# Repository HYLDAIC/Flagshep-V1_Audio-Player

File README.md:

# Flagshep V1 Audio Player

*During Playback*

## Overview
The **Flagshep** is a semi-portable open-source Audio Player designed to provide a reliable, high-quality offline listening experience. It's purpose is to be an alternative to advertisement-ridden subscription based streaming services. The pilot project includes the PCB design files, enclosure CAD models and firmware source code required to build upon, modify or simply take inspiration of the device.

# Features & Specifications 
## Features
- High Quality Audio Diffusion 
- USB-C Charging and Flashing 
## Specifications 
- **Processor :** ESP32 S3 (2 Core 240MHz, 2.4 GHz Wi-Fi 150 Mbps, Bluetooth 5 (LE) )
- **Audio Quality :** PCM5102A ; 16-32bit at 8kHz to 384kHz
- **Flash :** 8MB quad SPI Flash
- **RAM :** 8MB quad SPI SRAM
- **Display :** 0.96in 128x64px OLED TFT display
- **Input :** 6 Button Matrix
- **Storage :** MicroSD card slot
- **Battery :** 5000mAh LiPo with integrated charging and battery management
- **Connectors :** USB Type-C and TRS 3.5mm Audio Jack
- **Dimensions :** 98.7 x 76.8 x 34.7 mm (length-width-height)

# Design 

## Hardware & Included Sensors
- **Microcontroller :** ESP32 S3 Wroom 1
- **DAC Chip :** PCM5102A
- **Battery charging & Protection :** TP4056 & DW01A + FS8205A
- **Voltage Regulator (LDO) :** AP2112K-3.3
- **Battery Percentage Chip :**  MAX17048G+T10
- **Battery Connector :** JST XH-B2B-A

*Logic Depiction of the Hardware*

## Firmware 
- A simple loop that handles button presses, screen refreshes, audio streaming and battery capacity/optimizations; fairly simple
- More coming soon to a town near you!

# Enclosure & Build Instructions (Doesn't include pictures)
- M4 screwdriver
- 3D printed parts (Main, Top of your choosing, and Bottom cover)
- The PCB
- A flat Lithium Polymer battery (LiPo) with the connector JST-XH 2 pin
- 12 6-8mm screws M4 screws
- 12 6x6mm (M4) threaded heated inserts
- Formatted SD Card (FAT32,  exFAT ...) with the audio of your choice (mp3, WAV, FLAC, AAC, m4a)
- A Computer (Linux and or Windows 10-11) with VS Code and Platformio installed
- USB-C Data cable
- Soldering iron

  1. The Main 3D printed part should have prominent holes, 8 on the front side and 4 in the back
  2. Prepare heated element to 250 degrees Celsius (+/- 30)
  3. Place and slowly push in the threaded heated insert with the soldering iron into the hole until the mounting surface is flat (repeat 12 times)
  4. If the battery connector of the PCB isn't on the bottom face (face with no components), solder it on the bottom making sure to keep the same polarities
  5. Insert the SD card in the SD card slot
  6. Take the PCB and insert it inside the side with 8 screws, it should fit with the bottom four; screw it on (it should match with the outside holes on the side of the Main piece)
  7. Insert and screw in the Top cover with 4 screws
  8. Insert a LiPo battery in the bottom compartment and plug it in
  9. Screw in the bottom cover making sure not to break the cable of your battery
  10. Take a USB-C data cable and plug it into the board and the computer
  11. Compile the code given in the Github repo (check tutorials online if you are not sure about how to do this)
  12. Flash the code

# Successes & Future Improvements (Hardware focused)
## Successes
- The audio is smooth and doesn't have noticeable glitching or noise within playback
- A battery life of about 32-40 hours on a 5000mAh battery (~35h of playback in an room varying from 23 to 35 degrees Celsius)
- A smooth user experience; fairly intuitive button mapping, responsive menus and UI (tested by passing my friends the player and receiving feedback)
- An easily accessible and removable battery/screen (4 Screws each)
- Fairly resistant; could be dropped several times with no issues to the PCB (1m drop height)
- The PCB worked first try :)

## Future Improvements
The design has notable failure points that can't be addressed in version 1.1 and would need a more substantial redesign, here are some :
- The circuit drains significant amounts of battery on sleeping parts when the microcontroller is sleeping; physical software activated kill switch needed
- Due to bad design around the battery; the enclosure is huge (height)
- The ESP32 S3 is realistically overkill for the scope of this project AND wireless isn't the focus and could've been avoided
- Components are way too close together making assembly difficult 
- The lack of a knobs proves more difficult than expected
- The screen is really small (this was intended but a more substantial screen could've been afforded under this battery capacity)
- Visible and protruding screws
- Somewhat Heavy (battery)
- The battery percentage chip has interference issues with nearby components and should be placed closer to the battery's connector
- Adding test pads for important signals

Issues that weren't but can be easily addressed in version 1.2 :
- Outside ports are hard to access (too far from outside ridge)
- Thermal relief for ground pads NEED to be added

Personal issues with the design : 
- Many parts of the circuit could have been separated on different boards to permit easy fixing and maintenance (e.g. board 1; power, board 2; logic, etc)

## Plans for the project
Apart from version 1.2, I plan to remake the audio player in a couple of years after I have learned more about circuit design and embedded development.
For now, all the following improvements made to this project will made in the form of sporadic software improvements as I catch problems or wants with the device in my own usage.

# License
The license only applies to the PCB part of the design, not the code nor the 3D STEP files which are unlicensed

# Acknowledgements
## Help & Design inspirations 
- My non-technical friends for support & UX feedback
- r/PrintedCircuits for help with circuit design (https://www.reddit.com/r/PrintedCircuitBoard/)
- PocketMage by Ashtf at Talisman Designs (specs & features section and general design inspiration) (https://www.crowdsupply.com/talisman-design/pocketmage)
## Firmware
- Adafruit (GFX & SSD1306)
- ESP32-audioI2S by Schreibfaul1 (https://github.com/schreibfaul1/ESP32-audioI2S)

## Special Mention
The large reason of why I decided to commit to making this audio player was for my love of music that I'm sure others can relate to.
That said, during the development of the board, one of my favorite band disbanded.
As an homage to them and what their music meant to me, I chose to immortalize them on the surface of my PCB with their most popular instrumental. 

Again, this is a small tribute, but it may just last forever ;)

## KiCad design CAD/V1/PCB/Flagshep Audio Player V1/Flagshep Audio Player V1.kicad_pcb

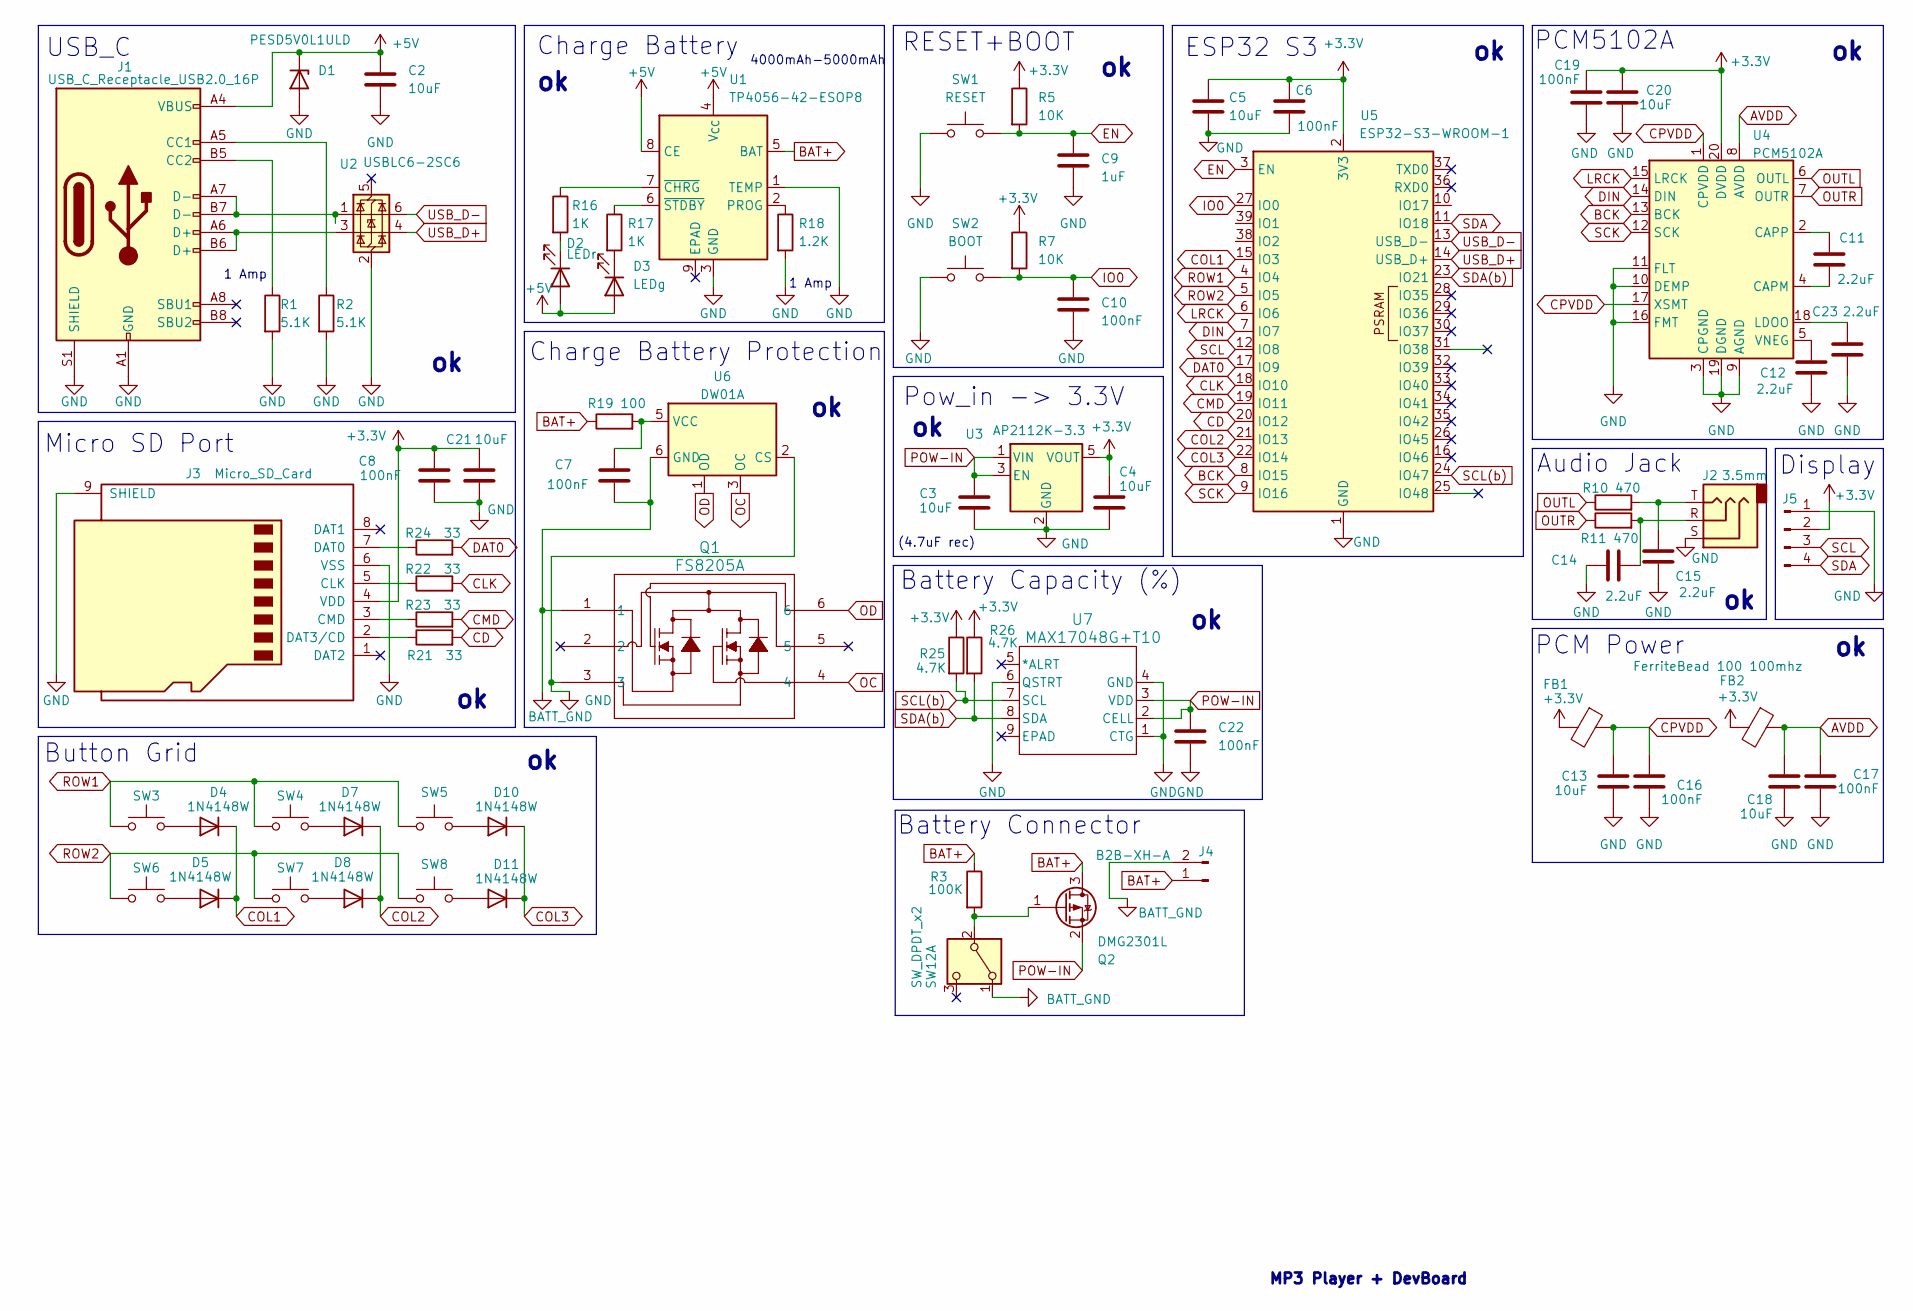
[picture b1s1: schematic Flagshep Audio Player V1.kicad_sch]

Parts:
C2, C13, C18, C20, C21: 10uF; C_0805_2012Metric_Pad1.18x1.45mm_HandSolder
C3, C4, C5: 10uF; R_0805_2012Metric_Pad1.20x1.40mm_HandSolder
C6: 100nF; R_0805_2012Metric_Pad1.20x1.40mm_HandSolder
C7, C8, C10, C16, C17, C19, C22: 100nF; C_0805_2012Metric_Pad1.18x1.45mm_HandSolder
C9: 1uF; R_0805_2012Metric_Pad1.20x1.40mm_HandSolder
C11, C12, C14, C15, C23: 2.2uF; C_0805_2012Metric_Pad1.18x1.45mm_HandSolder
D1: PESD5V0L1ULD; D_SOD-882D
D2: LEDr; LED_1206_3216Metric_Pad1.42x1.75mm_HandSolder
D3: LEDg; LED_1206_3216Metric_Pad1.42x1.75mm_HandSolder
D4, D5, D7, D8, D10, D11: 1N4148W; D_SOD-123
FB1, FB2: FerriteBead 100 100mhz; L_0805_2012Metric_Pad1.15x1.40mm_HandSolder
J1: USB_C_Receptacle_USB2.0_16P; USB_C_Receptacle_G-Switch_GT-USB-7010ASV
J2: 3.5mm; Jack_3.5mm_CUI_SJ-3523-SMT_Horizontal
J3: Micro_SD_Card; microSD_HC_Wuerth_693072010801
J4: B2B-XH-A; JST_XH_B2B-XH-A_1x02_P2.50mm_Vertical
J5: Conn_01x04_Pin; PinHeader_1x04_P2.54mm_Vertical
Q1: FS8205A; SOT-23-6_Handsoldering
Q2: DMG2301L; SOT-23
R1, R2: 5.1K; R_0805_2012Metric_Pad1.20x1.40mm_HandSolder
R3: 100K; R_0805_2012Metric_Pad1.20x1.40mm_HandSolder
R5, R7: 10K; R_0805_2012Metric_Pad1.20x1.40mm_HandSolder
R10, R11: 470; R_0805_2012Metric_Pad1.20x1.40mm_HandSolder
R16, R17: 1K; R_0805_2012Metric_Pad1.20x1.40mm_HandSolder
R18: 1.2K; R_0805_2012Metric_Pad1.20x1.40mm_HandSolder
R19: 100; R_0805_2012Metric_Pad1.20x1.40mm_HandSolder
R21, R22, R23, R24: 33; R_0805_2012Metric_Pad1.20x1.40mm_HandSolder
R25, R26: 4.7K; R_0805_2012Metric_Pad1.20x1.40mm_HandSolder
SW1: RESET; SW_SPST_B3U-1000P
SW2: BOOT; SW_SPST_B3U-1000P
SW3, SW4, SW5, SW6, SW7, SW8: Button_Switch_THT:SW_PUSH-12mm; SW_PUSH-12mm
SW12: SW_DPDT_x2; SW_CK_JS202011AQN_DPDT_Angled
U1: TP4056-42-ESOP8; SOIC-8-1EP_3.9x4.9mm_P1.27mm_EP2.41x3.3mm_ThermalVias
U2: USBLC6-2SC6; SOT-23-6
U3: AP2112K-3.3; SOT-23-5
U4: PCM5102A; TSSOP-20_4.4x6.5mm_P0.65mm
U5: ESP32-S3-WROOM-1
U6: DW01A; SOT-23-6_Handsoldering
U7: MAX17048G+T10; 21-0168E_T822-3_MXM

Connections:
+3.3V: C4.1, C5.1, C6.1, C8.2, C19.2, C20.2, C21.1, FB1.2, FB2.2, J3.4 (VDD), J5.2, R5.1, R7.1, R25.1, R26.1, U3.5 (VOUT), U4.20 (DVDD), U5.2 (3V3)
+5V: C2.1, D1.1 (K), D2.2 (A), D3.2 (A), J1.A4 (VBUS), J1.A9 (VBUS), J1.B4 (VBUS), J1.B9 (VBUS), U1.4 (V_{CC}), U1.8 (CE)
AVDD: C17.2, C18.2, FB2.1, U4.8 (AVDD)
BAT+: J4.1, Q2.3 (D), R3.1, R19.1, U1.5 (BAT)
BATT_GND: C7.2, J4.2, Q1.1, SW12.1 (A), U6.6 (GND)
BCK: U4.13 (BCK), U5.8 (IO15)
CD: R21.2, U5.20 (IO12)
CLK: R22.2, U5.18 (IO10)
CMD: R23.2, U5.19 (IO11)
COL1: D4.1 (K), D5.1 (K), U5.15 (IO3)
COL2: D7.1 (K), D8.1 (K), U5.21 (IO13)
COL3: D10.1 (K), D11.1 (K), U5.22 (IO14)
CPVDD: C13.2, C16.2, FB1.1, U4.1 (CPVDD), U4.17 (XSMT)
DAT0: R24.2, U5.17 (IO9)
DIN: U4.14 (DIN), U5.7 (IO7)
EN: C9.1, R5.2, SW1.2, U5.3 (EN)
GND: C2.2, C3.2, C4.2, C5.2, C6.2, C8.1, C9.2, C10.2, C12.2, C13.1, C14.2, C15.2, C16.1, C17.1, C18.1, C19.1, C20.1, C21.2, C22.2, C23.2, D1.2 (A), J1.A1 (GND), J1.A12 (GND), J1.B1 (GND), J1.B12 (GND), J1.S1 (SHIELD), J2.S, J3.6 (VSS), J3.9 (SHIELD), J5.1, Q1.3, R1.2, R2.2, R18.2, SW1.1, SW2.1, U1.1 (TEMP), U1.3 (GND), U2.2 (GND), U3.2 (GND), U4.3 (CPGND), U4.9 (AGND), U4.10 (DEMP), U4.11 (FLT), U4.16 (FMT), U4.19 (DGND), U5.1 (GND), U5.40 (GND), U5.41 (GND), U6.2 (CS), U7.1 (CTG), U7.4 (GND), U7.6 (QSTRT)
IO0: C10.1, R7.2, SW2.2, U5.27 (IO0)
LRCK: U4.15 (LRCK), U5.6 (IO6)
unnamed: C14.1, J2.R, R11.2
unnamed: C15.1, J2.T, R10.2
unnamed: D2.1 (K), R16.2
unnamed: D3.1 (K), R17.2
unnamed: D4.2 (A), SW3.2
unnamed: D5.2 (A), SW6.2
unnamed: D7.2 (A), SW4.2
unnamed: D8.2 (A), SW7.2
unnamed: D10.2 (A), SW5.2
unnamed: D11.2 (A), SW8.2
unnamed: J1.A5 (CC1), R2.1
unnamed: J1.B5 (CC2), R1.1
unnamed: J1.A6 (D+), J1.B6 (D+), U2.3 (I/O2)
unnamed: J1.A7 (D-), J1.B7 (D-), U2.1 (I/O1)
unnamed: J3.5 (CLK), R22.1
unnamed: J3.3 (CMD), R23.1
unnamed: J3.7 (DAT0), R24.1
unnamed: J3.2 (DAT3/CD), R21.1
unnamed: Q2.1 (G), R3.2, SW12.2 (B)
unnamed: R18.1, U1.2 (PROG)
unnamed: R16.1, U1.7 (~CHRG)
unnamed: R17.1, U1.6 (~STDBY)
unnamed: C11.2, U4.4 (CAPM)
unnamed: C11.1, U4.2 (CAPP)
unnamed: C23.1, U4.18 (LDOO)
unnamed: C12.1, U4.5 (VNEG)
unnamed: C7.1, R19.2, U6.5 (VCC)
OC: Q1.4, U6.3 (OC)
OD: Q1.6, U6.1 (OD)
OUTL: R10.1, U4.6 (OUTL)
OUTR: R11.1, U4.7 (OUTR)
POW-IN: C3.1, C22.1, Q2.2 (S), U3.1 (VIN), U3.3 (EN), U7.2 (CELL), U7.3 (VDD)
ROW1: SW3.1, SW4.1, SW5.1, U5.4 (IO4)
ROW2: SW6.1, SW7.1, SW8.1, U5.5 (IO5)
SCK: U4.12 (SCK), U5.9 (IO16)
SCL: J5.3, U5.12 (IO8)
SCL(b): R25.2, U5.24 (IO47), U7.7 (SCL)
SDA: J5.4, U5.11 (IO18)
SDA(b): R26.2, U5.23 (IO21), U7.8 (SDA)
USB_D+: U2.4 (I/O2), U5.14 (USB_D+)
USB_D-: U2.6 (I/O1), U5.13 (USB_D-)

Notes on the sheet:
ESP32 S3
1 Amp
PCM Power
Charge Battery Protection
PCM5102A
Pow_in -> 3.3V
MP3 Player + DevBoard
Micro SD Port
RESET+BOOT
Battery Capacity (%)
Audio Jack
Battery Connector
Button Grid
Display
4000mAh-5000mAh
Charge Battery
USB_C
(4.7uF rec)

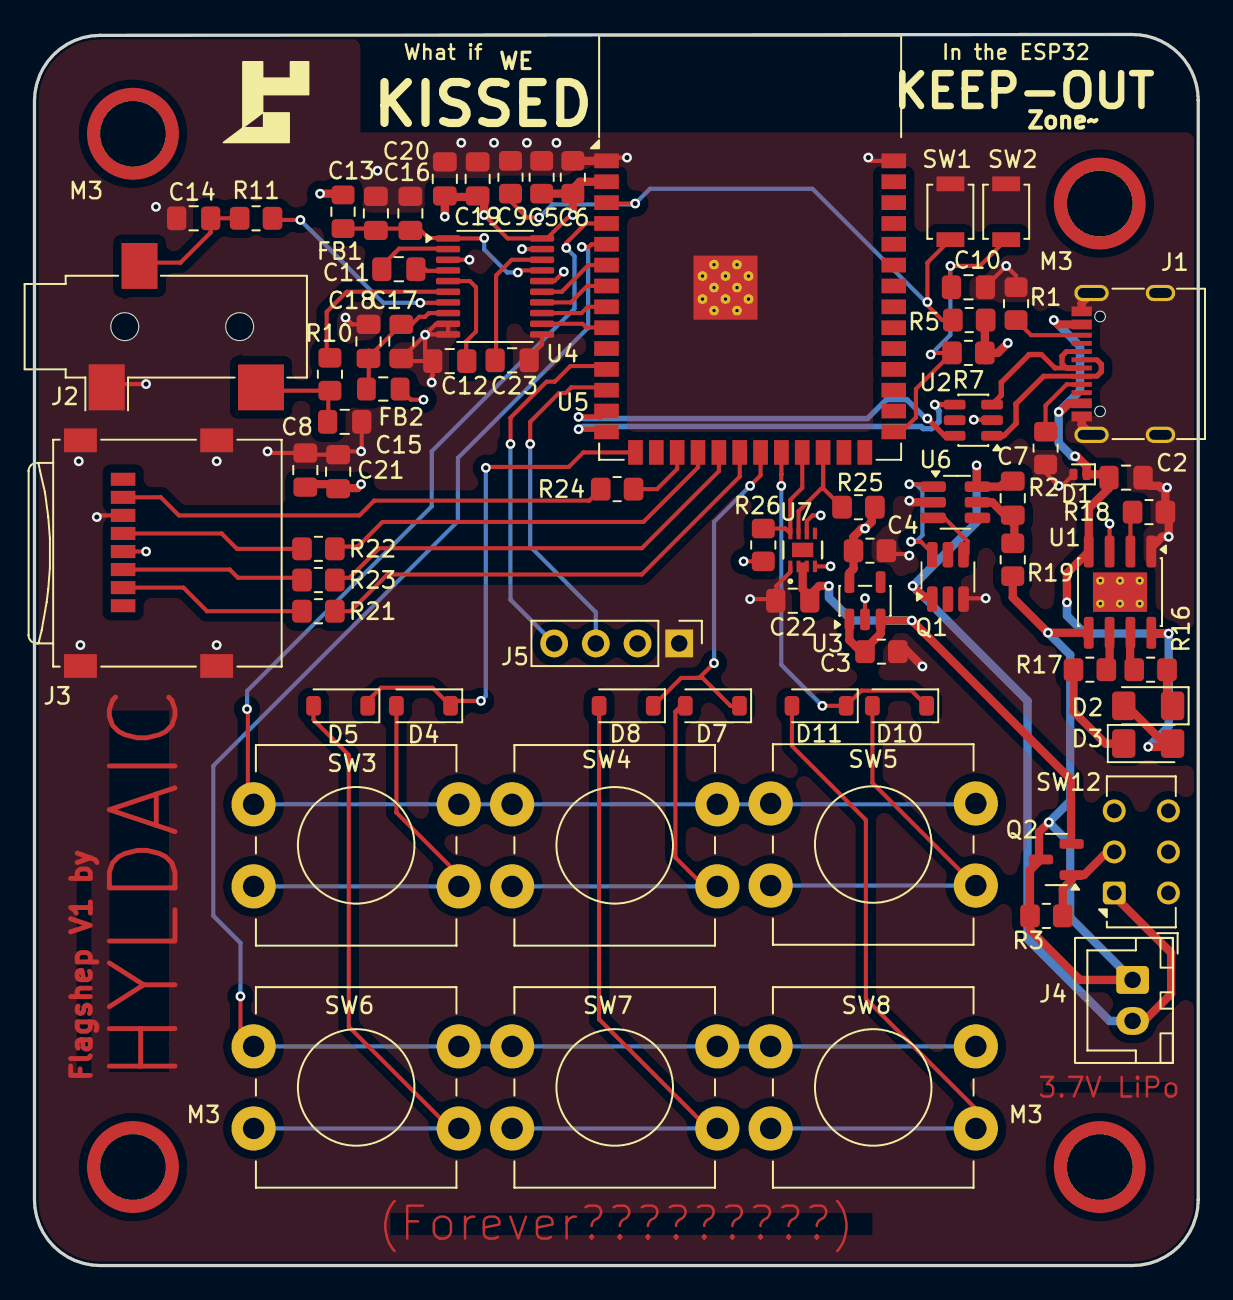
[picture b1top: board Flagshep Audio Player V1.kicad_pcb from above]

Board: 4 copper layers, 70.9 x 75.0 mm, 75 parts (0 on the bottom side), 60 nets.

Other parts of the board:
M3, M3#2: MountingHole_3.2mm_M3_DIN965_Pad_TopBottom

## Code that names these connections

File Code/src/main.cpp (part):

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  #define DBG_PRINTLN(x)
#endif

const uint8_t COL1 = 3;
const uint8_t COL2 = 13;
const uint8_t COL3 = 14;
const uint8_t ROW1 = 4;
const uint8_t ROW2 = 5;

const uint8_t ROWS = 2;
const uint8_t COLS = 3;
const uint8_t rowPins[ROWS] = {ROW1, ROW2};
const uint8_t colPins[COLS] = {COL1, COL2, COL3};

void enterDeepSleep();

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  delay(20);

  //ROW2 to exit deep sleep
  rtc_gpio_init((gpio_num_t)ROW2);
  rtc_gpio_set_direction((gpio_num_t)ROW2, RTC_GPIO_MODE_OUTPUT_ONLY);
  rtc_gpio_set_level((gpio_num_t)ROW2, 1);
  rtc_gpio_hold_en((gpio_num_t)ROW2);

  const gpio_num_t wakeCols[] = {
    (gpio_num_t)COL1, (gpio_num_t)COL2, (gpio_num_t)COL3
  };

  uint64_t wakeMask = 0;
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void setup() {
  DBG_BEGIN(9600);

  //Release ROW2's hold and hand all the wake-related pins back to normal digital GPIO 
  rtc_gpio_hold_dis((gpio_num_t)ROW2);
  rtc_gpio_deinit((gpio_num_t)ROW2);
  rtc_gpio_deinit((gpio_num_t)COL1);
  rtc_gpio_deinit((gpio_num_t)COL2);
  rtc_gpio_deinit((gpio_num_t)COL3);

  esp_sleep_wakeup_cause_t wakeReason = esp_sleep_get_wakeup_cause();
  DBG_PRINT("Wakeup cause: ");
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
